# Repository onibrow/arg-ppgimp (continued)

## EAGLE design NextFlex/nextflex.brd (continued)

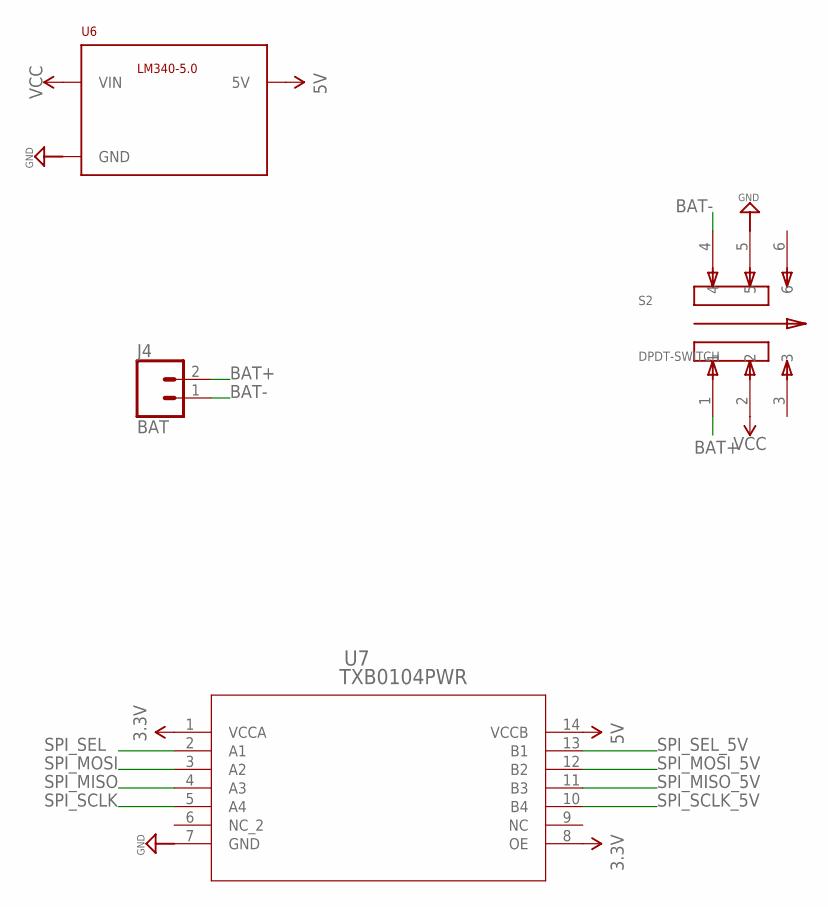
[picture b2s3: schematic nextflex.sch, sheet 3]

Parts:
J4: BAT; 1X02
S2: DPDT-SWITCH; SW_JS202011SCQN
U6: LM340MPX-5.0230; SOT230P700X180-4N
U7: TXB0104PWR; PW14

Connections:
3.3V: U7.1 (VCCA), U7.8 (OE); also elsewhere on the board
5V: U6.3 (5V), U7.14 (VCCB); also elsewhere on the board
BAT+: J4.2, S2.1
BAT-: J4.1, S2.4
GND: S2.5, U6.2 (GND), U6.4 (GND), U7.7 (GND); also elsewhere on the board
SPI_MISO: U7.4 (A3); also elsewhere on the board
SPI_MISO_5V: U7.11 (B3); also elsewhere on the board
SPI_MOSI: U7.3 (A2); also elsewhere on the board
SPI_MOSI_5V: U7.12 (B2); also elsewhere on the board
SPI_SCLK: U7.5 (A4); also elsewhere on the board
SPI_SCLK_5V: U7.10 (B4); also elsewhere on the board
SPI_SEL: U7.2 (A1); also elsewhere on the board
SPI_SEL_5V: U7.13 (B1); also elsewhere on the board
VCC: S2.2, U6.1 (VIN); also elsewhere on the board

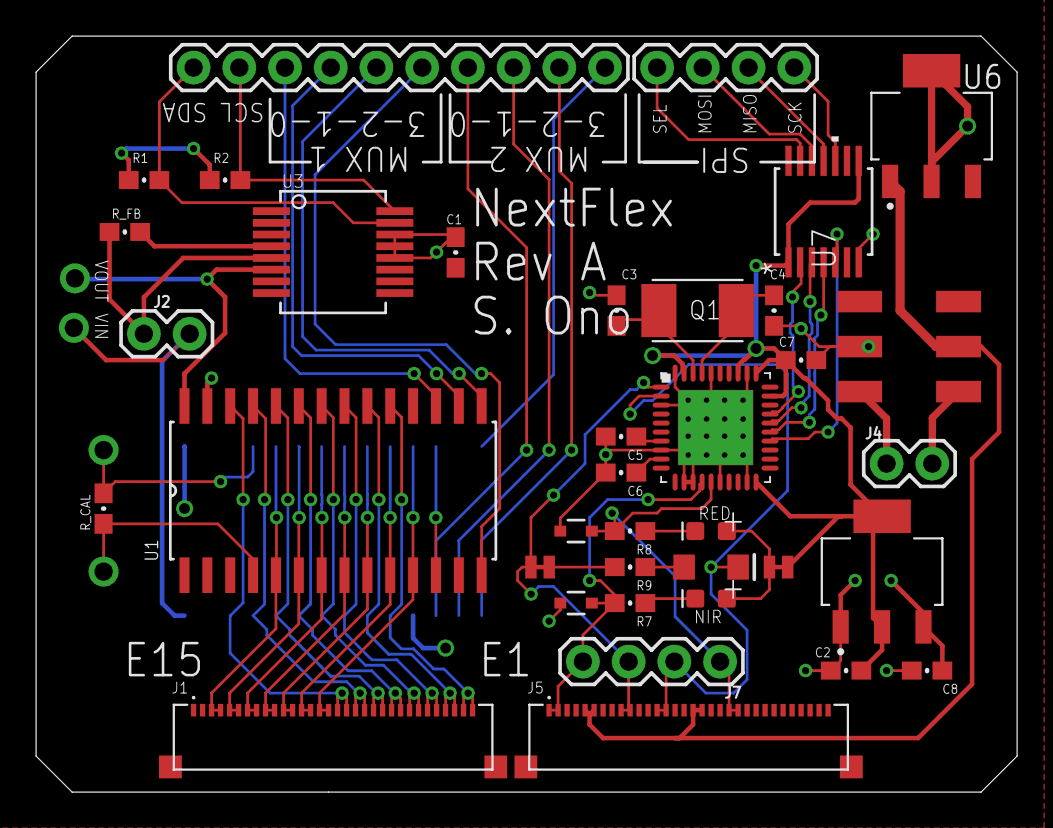
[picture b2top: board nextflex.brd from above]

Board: 2 copper layers, 54.5 x 42.0 mm, 42 parts (1 on the bottom side), 58 nets.

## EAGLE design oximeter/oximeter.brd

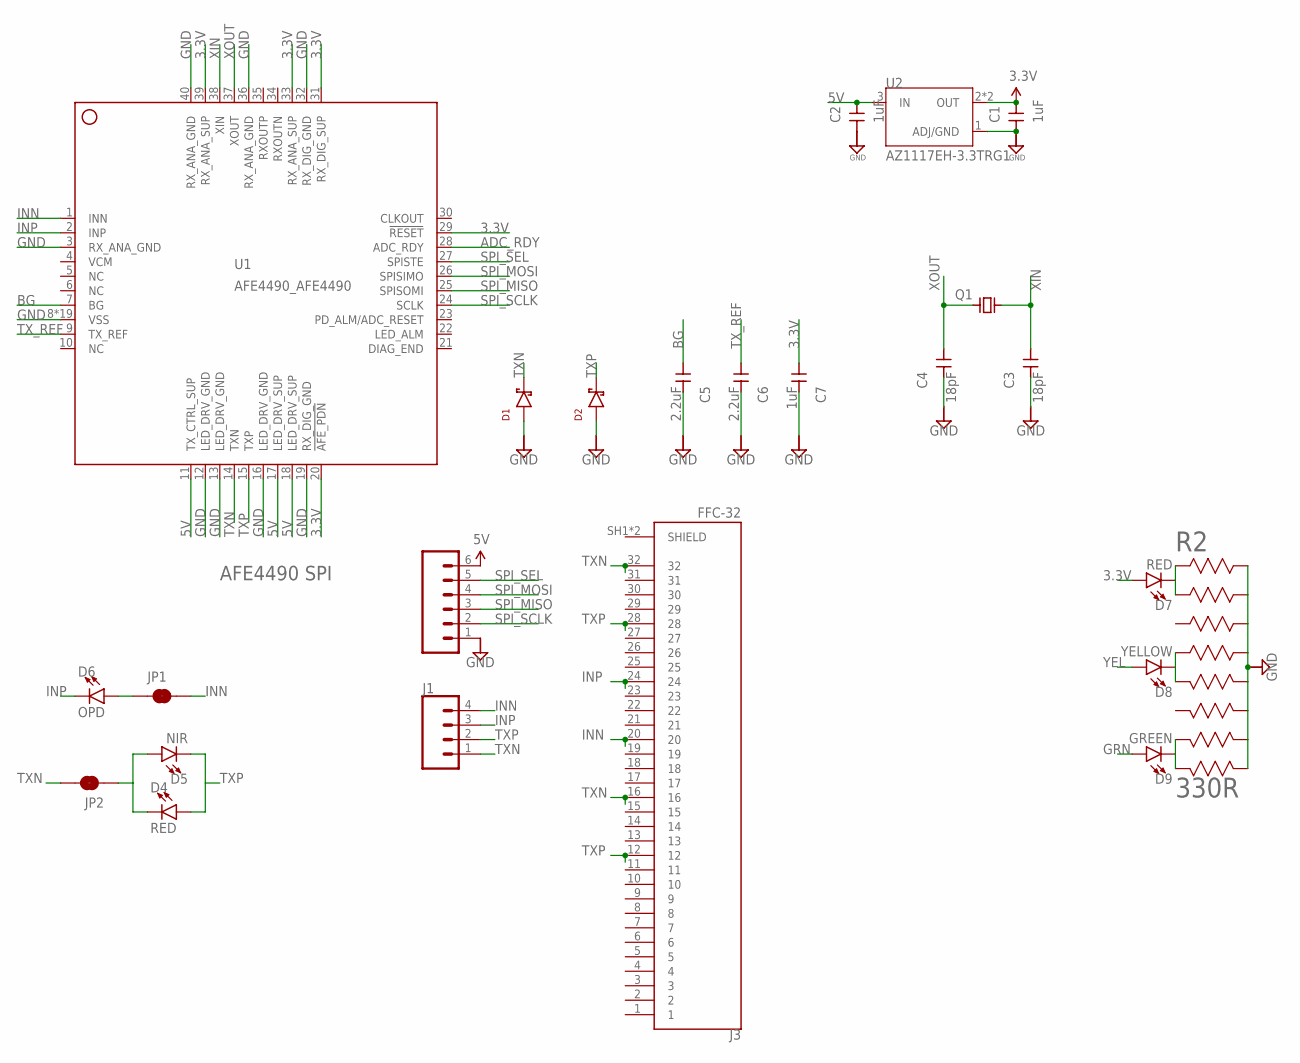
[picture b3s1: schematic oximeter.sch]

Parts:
C1, C2, C7: 1uF; 0603-CAP
C3, C4: 18pF; 0603-CAP
C5, C6: 2.2uF; 0603-CAP
D1, D2: DIODE_CZRU; CZRU
D4, D7: RED; LED-0603
D5: NIR; LED-0603
D6: OPD; LED-1206
D8: YELLOW; LED-0603
D9: GREEN; LED-0603
J1: CONN_04; 1X04
J2: CONN_06SILK_FEMALE_PTH; 1X06
J3: FFC-32; MOLEX_503480-3200
JP1, JP2: JUMPER-SMT_2_NC_TRACE_NO-SILK; SMT-JUMPER_2_NC_TRACE_NO-SILK
Q1: CRYSTAL_ECS_8MHZ; XTAL_ECS-80-18-5PX-TR
R2: 330R; EXB2HV
U1: AFE4490_AFE4490; AFE4490_QFN40-6X6
U2: AZ1117EH-3.3TRG1; SOT230P700X180-4N

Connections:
3.3V: C1.1, C7.1, D7.A, U1.20 (!AFE_PDN), U1.29 (!RESET), U1.31 (RX_DIG_SUP), U1.33 (RX_ANA_SUP), U1.39 (RX_ANA_SUP), U2.2 (OUT), U2.4 (OUT)
5V: C2.1, J2.6, U1.11 (TX_CTRL_SUP), U1.17 (LED_DRV_SUP), U1.18 (LED_DRV_SUP), U2.3 (IN)
ADC_RDY: U1.28 (ADC_RDY)
BG: C5.1, U1.7 (BG)
GND: C1.2, C2.2, C3.2, C4.2, C5.2, C6.2, C7.2, D1.P, D2.P, J2.1, R2.9, R2.10, R2.11, R2.12, R2.13, R2.14, R2.15, R2.16, U1.3 (RX_ANA_GND), U1.8 (VSS), U1.12 (LED_DRV_GND), U1.13 (LED_DRV_GND), U1.16 (LED_DRV_GND), U1.19 (RX_DIG_GND), U1.32 (RX_DIG_GND), U1.36 (RX_ANA_GND), U1.40 (RX_ANA_GND), U1.EXP@1 (VSS), U1.EXP@2 (VSS), U1.EXP@3 (VSS), U1.EXP@4 (VSS), U1.EXP@5 (VSS), U1.EXP@6 (VSS), U1.EXP@7 (VSS), U1.EXP@8 (VSS), U1.EXP@9 (VSS), U1.EXP@10 (VSS), U1.EXP@11 (VSS), U1.EXP@12 (VSS), U1.EXP@13 (VSS), U1.EXP@14 (VSS), U1.EXP@15 (VSS), U1.EXP@16 (VSS), U1.PWR@1 (VSS), U1.PWR@2 (VSS), U2.1 (ADJ/GND)
GRN: D9.A
INN: J1.4, J3.20, JP1.2, U1.1 (INN)
INN_BUF: D6.A, JP1.1
INP: D6.C, J1.3, J3.24, U1.2 (INP)
unnamed: D7.C, R2.1, R2.2
unnamed: D8.C, R2.4, R2.5
unnamed: D9.C, R2.7, R2.8
SPI_MISO: J2.3, U1.25 (SPISOMI)
SPI_MOSI: J2.4, U1.26 (SPISIMO)
SPI_SCLK: J2.2, U1.24 (SCLK)
SPI_SEL: J2.5, U1.27 (SPISTE)
TXN: D1.N, J1.1, J3.16, J3.32, JP2.2, U1.14 (TXN)
TXN_BUF: D4.C, D5.A, JP2.1
TXP: D2.N, D4.A, D5.C, J1.2, J3.12, J3.28, U1.15 (TXP)
TX_REF: C6.1, U1.9 (TX_REF)
XIN: C3.1, Q1.1 (A), U1.38 (XIN)
XOUT: C4.1, Q1.2 (B), U1.37 (XOUT)
YEL: D8.A

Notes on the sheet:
AFE4490 SPI

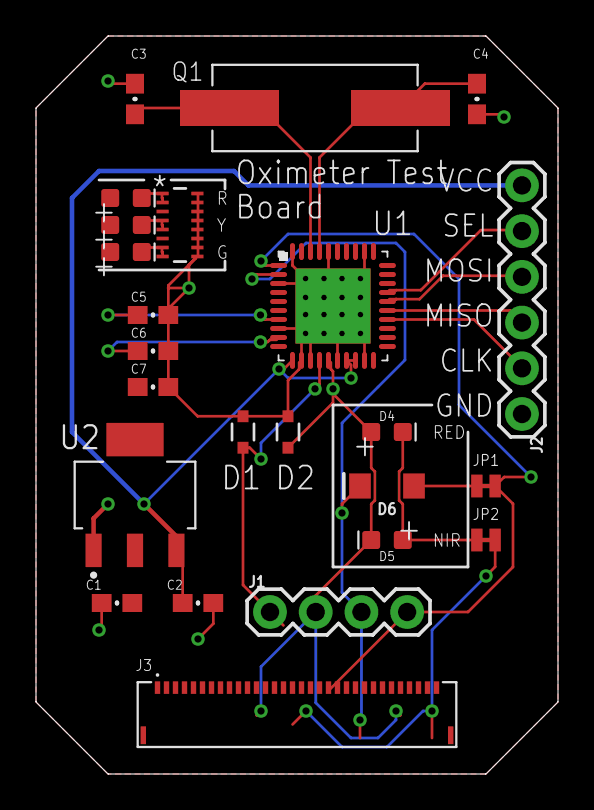
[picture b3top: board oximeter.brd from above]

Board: 2 copper layers, 29.0 x 41.0 mm, 24 parts (0 on the bottom side), 20 nets.

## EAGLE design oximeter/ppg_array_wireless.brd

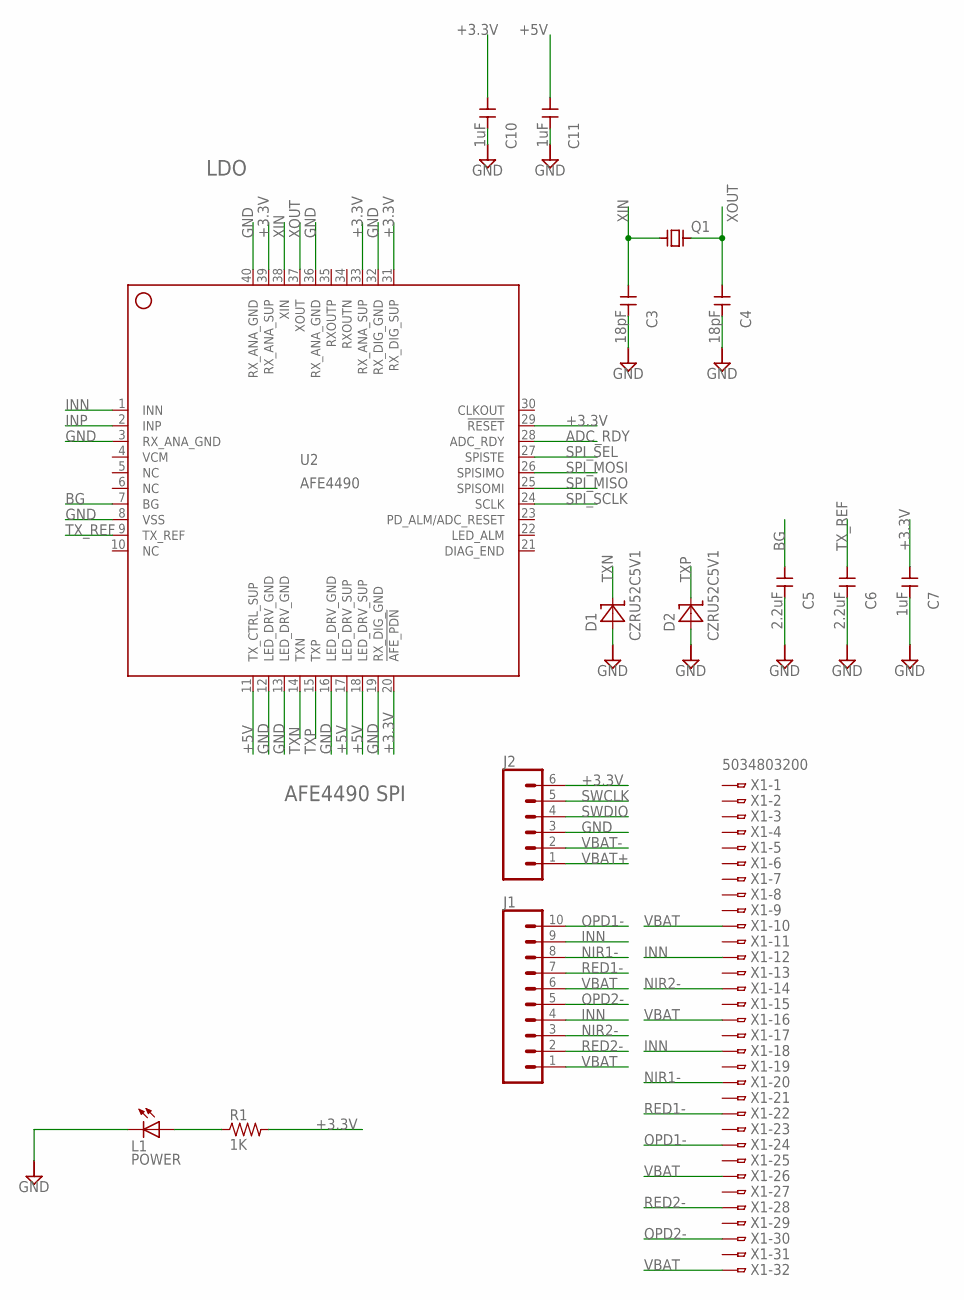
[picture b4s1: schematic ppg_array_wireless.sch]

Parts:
C3, C4: 18pF; 0603-CAP
C5, C6: 2.2uF; 0603-CAP
C7, C10, C11: 1uF; 0603-CAP
D1, D2: CZRU52C5V1
J1: CONN_10"; 1X10
J2: CONN_06SILK_FEMALE_PTH; 1X06
L1: POWER; CHIP-LED0603
Q1: CRYSTAL_ECS_8MHZ; XTAL_ECS-80-18-5PX-TR
R1: 1K; R0603
U2: AFE4490; QFN40-6X6
X1: 5034803200

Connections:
+3.3V: C7.1, C10.1, J2.6, R1.2, U2.20 (!AFE_PDN), U2.29 (!RESET), U2.31 (RX_DIG_SUP), U2.33 (RX_ANA_SUP), U2.39 (RX_ANA_SUP)
+5V: C11.1, U2.11 (TX_CTRL_SUP), U2.17 (LED_DRV_SUP), U2.18 (LED_DRV_SUP)
ADC_RDY: U2.28 (ADC_RDY)
BG: C5.1, U2.7 (BG)
GND: C3.2, C4.2, C5.2, C6.2, C7.2, C10.2, C11.2, D1.A, D2.A, J2.3, L1.C, U2.3 (RX_ANA_GND), U2.8 (VSS), U2.12 (LED_DRV_GND), U2.13 (LED_DRV_GND), U2.16 (LED_DRV_GND), U2.19 (RX_DIG_GND), U2.32 (RX_DIG_GND), U2.36 (RX_ANA_GND), U2.40 (RX_ANA_GND), U2.EXP@1 (GND), U2.EXP@2 (GND), U2.EXP@3 (GND), U2.EXP@4 (GND), U2.EXP@5 (GND), U2.EXP@6 (GND), U2.EXP@7 (GND), U2.EXP@8 (GND), U2.EXP@9 (GND), U2.EXP@10 (GND), U2.EXP@11 (GND), U2.EXP@12 (GND), U2.EXP@13 (GND), U2.EXP@14 (GND), U2.EXP@15 (GND), U2.EXP@16 (GND), U2.PWR@1 (GND), U2.PWR@2 (GND)
INN: J1.4, J1.9, U2.1 (INN), X1.12, X1.18
INP: U2.2 (INP)
unnamed: L1.A, R1.1
NIR1-: J1.8, X1.20
NIR2-: J1.3, X1.14
OPD1-: J1.10, X1.24
OPD2-: J1.5, X1.30
RED1-: J1.7, X1.22
RED2-: J1.2, X1.28
SPI_MISO: U2.25 (SPISOMI)
SPI_MOSI: U2.26 (SPISIMO)
SPI_SCLK: U2.24 (SCLK)
SPI_SEL: U2.27 (SPISTE)
SWCLK: J2.5
SWDIO: J2.4
TXN: D1.C, U2.14 (TXN)
TXP: D2.C, U2.15 (TXP)
TX_REF: C6.1, U2.9 (TX_REF)
VBAT: J1.1, J1.6, X1.10, X1.16, X1.26, X1.32
VBAT+: J2.1
VBAT-: J2.2
XIN: C3.1, Q1.1 (A), U2.38 (XIN)
XOUT: C4.1, Q1.2 (B), U2.37 (XOUT)

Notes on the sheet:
LDO
AFE4490 SPI

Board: 2 copper layers, 16 parts (0 on the bottom side), 18 nets, no tracks yet.

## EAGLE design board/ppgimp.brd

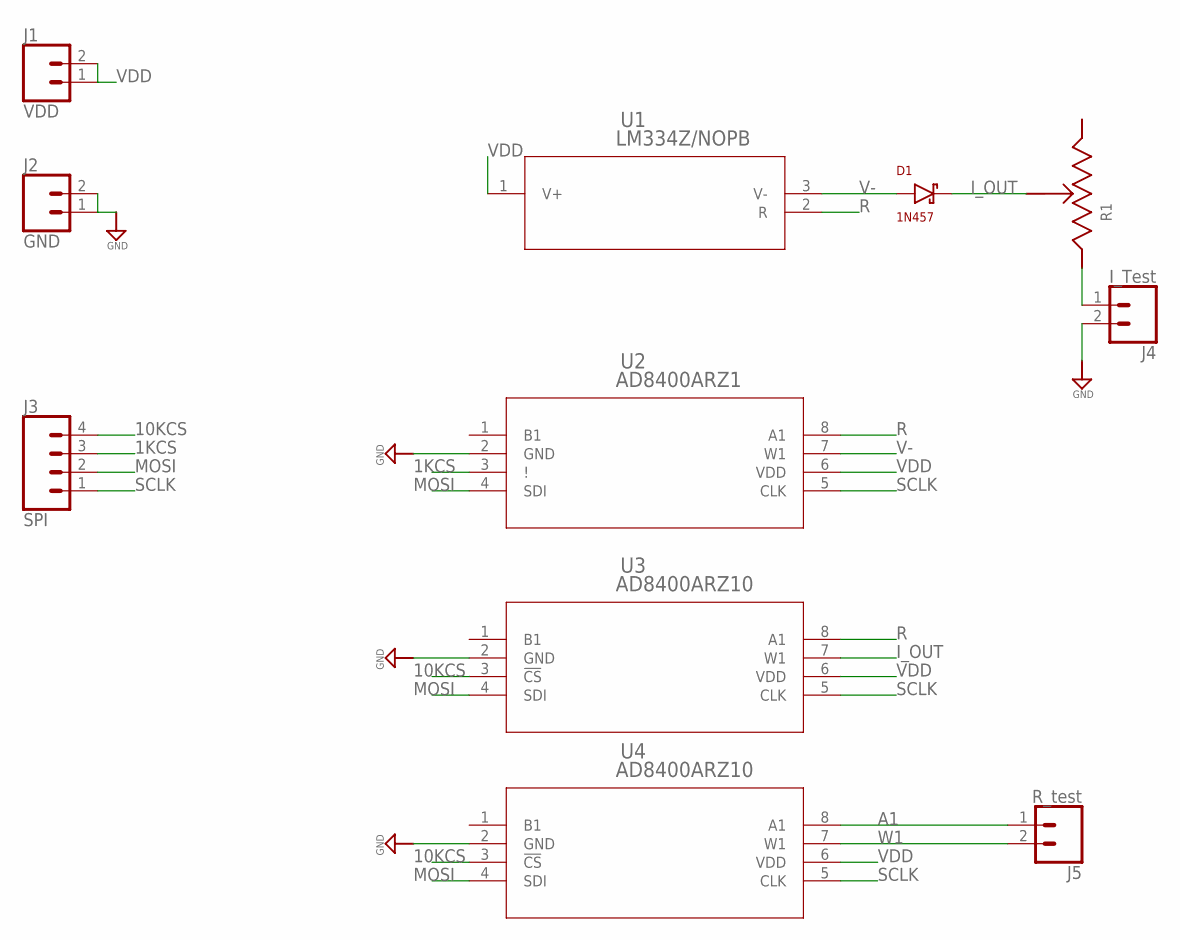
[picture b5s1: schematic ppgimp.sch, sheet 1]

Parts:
D1: 1N457; DIODE_THRU
J1: VDD; 1X02
J2: GND; 1X02
J3: SPI; 1X04
J4: I_Test; 1X02
J5: R_test; 1X02
R1: POT-3PIN
U1: LM334Z/NOPB; Z03A
U2: AD8400ARZ1; R_8
U3, U4: AD8400ARZ10; R_8

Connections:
1KCS: J3.3, U2.3 (!)
10KCS: J3.4, U3.3 (!CS), U4.3 (!CS)
A1: J5.1, U4.8 (A1)
GND: J2.1, J2.2, J4.2, U2.2 (GND), U3.2 (GND), U4.2 (GND); also elsewhere on the board
I_OUT: D1.2 (N), R1.2, U3.7 (W1)
MOSI: J3.2, U2.4 (SDI), U3.4 (SDI), U4.4 (SDI)
unnamed: J4.1, R1.3
R: U1.2 (R), U2.8 (A1), U3.8 (A1)
SCLK: J3.1, U2.5 (CLK), U3.5 (CLK), U4.5 (CLK)
V-: D1.1, U1.3 (V-), U2.7 (W1)
VDD: J1.1, J1.2, U1.1 (V+), U2.6 (VDD), U3.6 (VDD), U4.6 (VDD); also elsewhere on the board
W1: J5.2, U4.7 (W1)

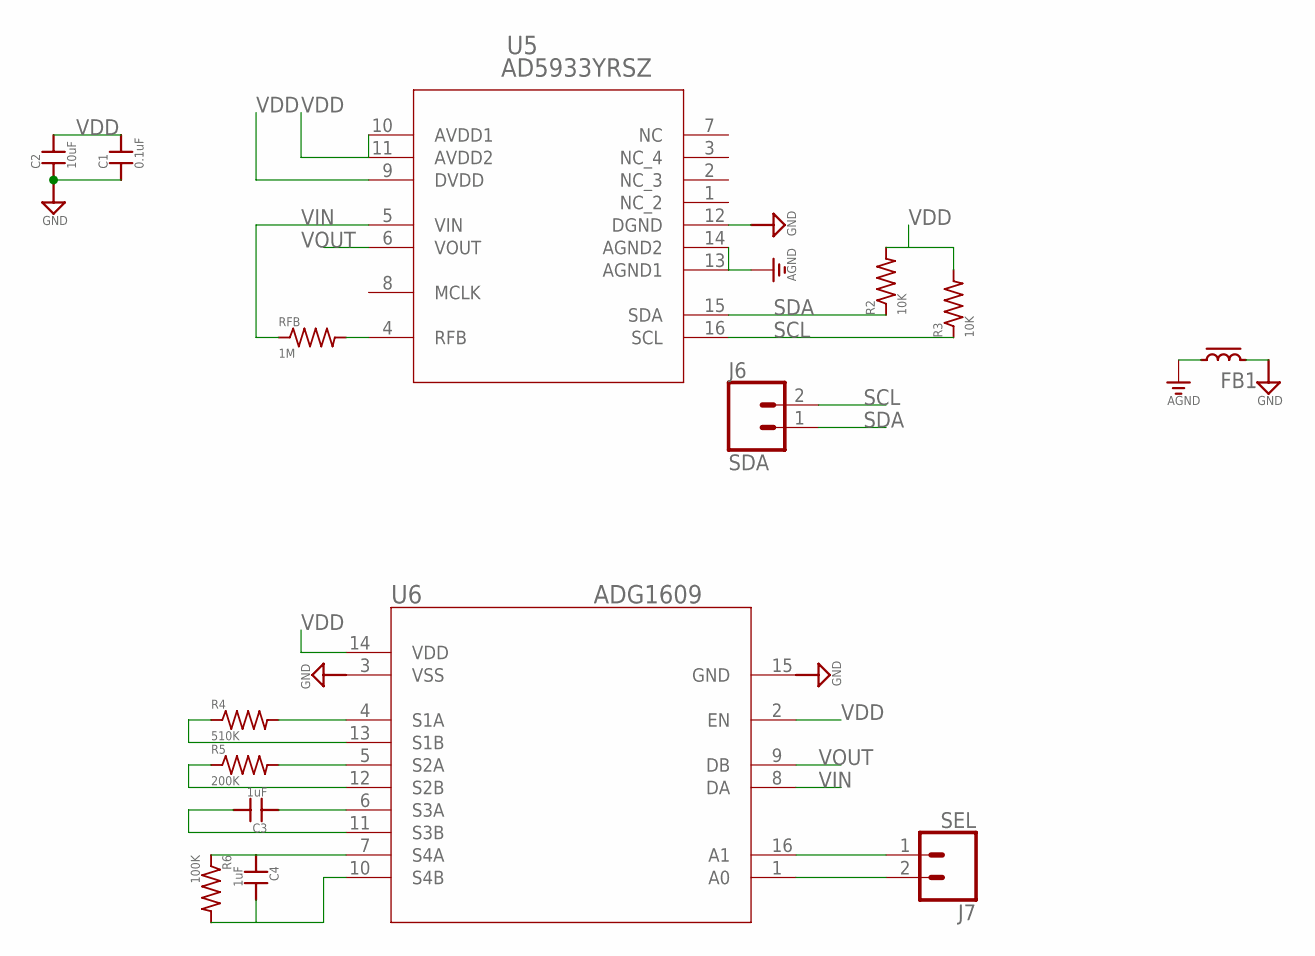
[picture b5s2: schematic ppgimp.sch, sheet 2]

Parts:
C1: 0.1uF; 0603-CAP
C2: 10uF; 0603-CAP
C3, C4: 1uF; 0603-CAP
FB1: FERRITE; 0603-FERR
J6: SDA; 1X02
J7: SEL; 1X02
R2, R3: 10K; R0603
R4: 510K; R0603
R5: 200K; R0603
R6: 100K; R0603
RFB: 1M; R0603
U5: AD5933YRSZ; RS_16
U6: ADG1609; RU_16

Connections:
AGND: FB1.1, U5.13 (AGND1), U5.14 (AGND2)
GND: C1.1, C2.1, FB1.2, U5.12 (DGND), U6.3 (VSS), U6.15 (GND); also elsewhere on the board
unnamed: RFB.2, U5.4 (RFB)
unnamed: J7.1, U6.16 (A1)
unnamed: J7.2, U6.1 (A0)
unnamed: R4.2, U6.4 (S1A)
unnamed: R4.1, U6.13 (S1B)
unnamed: R5.2, U6.5 (S2A)
unnamed: R5.1, U6.12 (S2B)
unnamed: C3.1, U6.6 (S3A)
unnamed: C3.2, U6.11 (S3B)
unnamed: C4.1, R6.1, U6.7 (S4A)
unnamed: C4.2, R6.2, U6.10 (S4B)
SCL: J6.2, R3.1, U5.16 (SCL)
SDA: J6.1, R2.1, U5.15 (SDA)
VDD: C1.2, C2.2, R2.2, R3.2, U5.9 (DVDD), U5.10 (AVDD1), U5.11 (AVDD2), U6.2 (EN), U6.14 (VDD); also elsewhere on the board
VIN: RFB.1, U5.5 (VIN), U6.8 (DA)
VOUT: U5.6 (VOUT), U6.9 (DB)

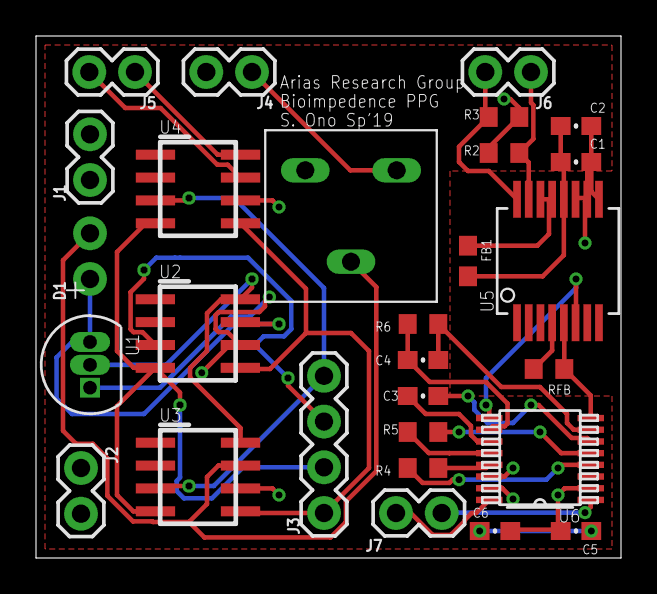
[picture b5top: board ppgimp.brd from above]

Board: 2 copper layers, 32.5 x 29.0 mm, 28 parts (0 on the bottom side), 28 nets.

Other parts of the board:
C5: 0.1uF; 0603-CAP
C6: 10uF; 0603-CAP

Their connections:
GND: C5.1, C6.1; also elsewhere on the board
VDD: C5.2, C6.2; also elsewhere on the board

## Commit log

2019-02-22 start taking notes for the ucsd module
2019-02-22 fix picture
2019-02-22 add spec table
2019-02-22 update current stuff
2019-02-22 notes on lm334
2019-02-22 update gitignore
2019-02-23 start working on the board
2019-02-24 add more impedence chip stuff
2019-02-24 get current source testing done
2019-02-26 do more research hook up ad5399
2019-03-01 finish up test board
2019-03-01 fix project description
2019-03-12 finalize prototype
2019-05-13 rename board
2019-05-13 get current source code working
2019-09-04 start oximeter board
2019-09-19 big boi commit
2019-09-19 send boards out for production and fix imp test code
2019-10-19 Fix the SS line and geprogram the AFE properly
2019-11-02 fix control2 register settings
2019-11-05 more nextflex progress
2019-11-06 finish rev a of nextflex
2019-11-06 Add bom and clp files for jcl
2019-11-18 Fix reads and push pull - leds light up and doesnt get hot but stil no data
2019-11-21 fix registers
2019-12-01 update firmware for electrodes and ox
2019-12-02 small fixes for anode cathone config
2019-12-03 Start final revision
2019-12-03 more work on firmware, electrodes work
2019-12-03 fix cs pin for mippe 32u4
2019-12-05 place final revision order for next flex
2019-12-18 final firmware revision
